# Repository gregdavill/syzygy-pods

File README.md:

# SYZYGY pods
This repository contains open source hardware SYZYGY pods designs
All repos are in KiCad format, some may require the use of KiCad nightly

---

SYZYGY is an FPGA expansion standard for medium to high speed interfaces. Learn more and check out the specifications here: [https://syzygyfpga.io/](https://syzygyfpga.io/)

* __lvds-10.1"-panel__ - 10.1" 1280x800 LVDS LCD + PMIC
* __ds90c124-deserializer__ - 1 to 24bit deserialzer
* __sii9022a__ - HDMI transmitter
* __can__ - MCP25625 based CAN controller

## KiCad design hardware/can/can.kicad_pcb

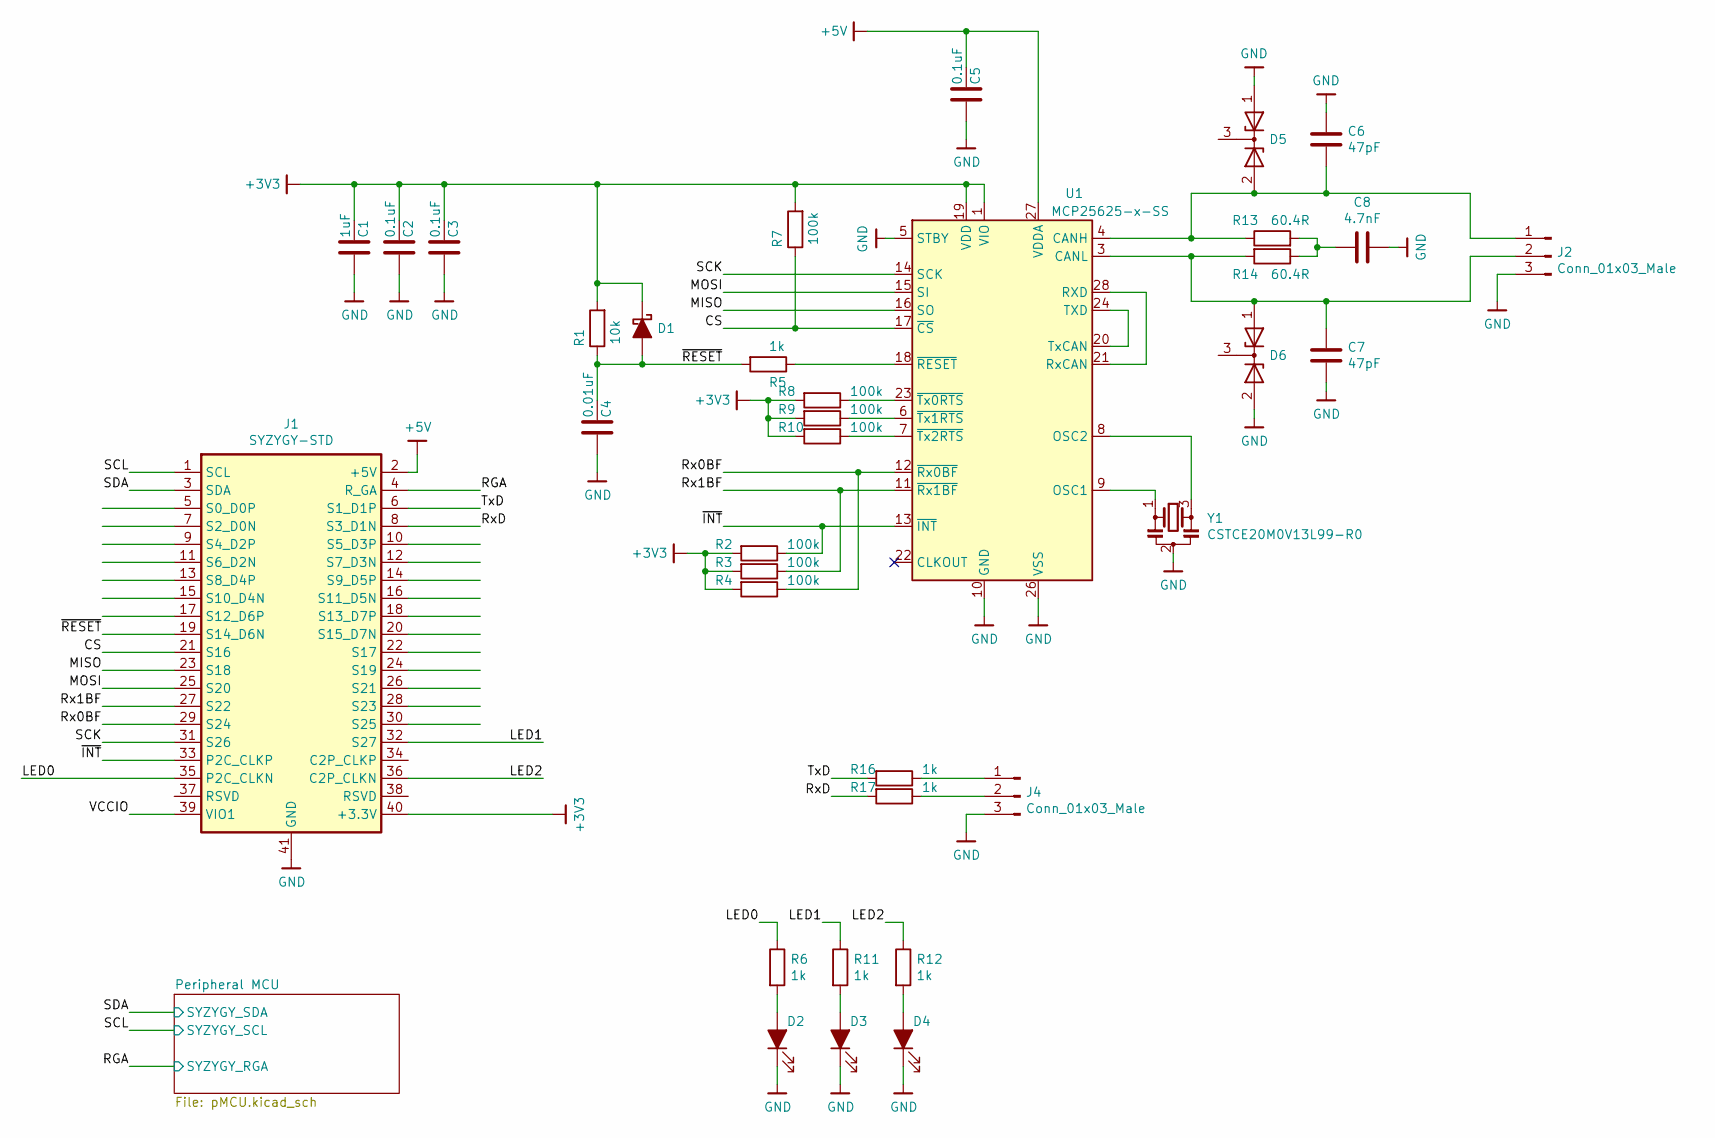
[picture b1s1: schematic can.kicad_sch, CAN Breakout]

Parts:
C1: 1uF; C_0402_1005Metric
C2, C3, C5: 0.1uF; C_0402_1005Metric
C4: 0.01uF; C_0402_1005Metric
C6, C7: 47pF; C_0805_2012Metric
C8: 4.7nF; C_0402_1005Metric
D1: D_Schottky_ALT; D_SOD-523
D2, D3, D4: LED_ALT; LED_0402_1005Metric
D5, D6: D_Zener_x2_KCom_AAK; SOT-23
J1: SYZYGY-STD; SYZYGY_standard_pod
J2: Conn_01x03_Male; PhoenixContact_MCV_1,5_3-G-3.5_1x03_P3.50mm_Vertical
J4: Conn_01x03_Male; PinHeader_1x03_P2.54mm_Vertical
R1: 10k; R_0402_1005Metric
R2, R3, R4, R7, R8, R9, R10: 100k; R_0402_1005Metric
R5, R6, R11, R12, R16, R17: 1k; R_0402_1005Metric
R13, R14: 60.4R; R_0805_2012Metric
U1: MCP25625-x-SS; SSOP-28_5.3x10.2mm_P0.65mm
Y1: CSTCE20M0V13L99-R0; Resonator_SMD_muRata_CSTxExxV-3Pin_3.0x1.1mm

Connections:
+3V3: C1.1, C2.1, C3.1, D1.1 (K), J1.40 (+3.3V), R1.2, R2.2, R3.2, R4.2, R7.2, R8.2, R9.2, R10.2, U1.1 (VIO), U1.19 (VDD); also elsewhere on the board
+5V: C5.1, J1.2 (+5V), U1.27 (VDDA)
/CS: J1.21 (S16), R7.1, U1.17 (~CS)
/LED0: J1.35 (P2C_CLKN), R6.1
/LED1: J1.32 (S27), R11.1
/LED2: J1.36 (C2P_CLKN), R12.1
/MISO: J1.23 (S18), U1.16 (SO)
/MOSI: J1.25 (S20), U1.15 (SI)
/RGA: J1.4 (R_GA); also elsewhere on the board
/Rx0BF: J1.29 (S24), R4.1, U1.12 (~Rx0BF)
/Rx1BF: J1.27 (S22), R3.1, U1.11 (~Rx1BF)
/RxD: J1.8 (S3_D1N), R17.2
/SCK: J1.31 (S26), U1.14 (SCK)
/SCL: J1.1 (SCL); also elsewhere on the board
/SDA: J1.3 (SDA); also elsewhere on the board
/TxD: J1.6 (S1_D1P), R16.2
/~INT: J1.33 (P2C_CLKP), R2.1, U1.13 (~INT)
/~RESET: C4.1, D1.2 (A), J1.19 (S14_D6N), R1.1, R5.2
GND: C1.2, C2.2, C3.2, C4.2, C5.2, C6.2, C7.1, C8.2, D2.1 (K), D3.1 (K), D4.1 (K), D5.1 (A), D6.2 (A), J1.41 (GND), J2.3, J4.3, U1.5 (STBY), U1.10 (GND), U1.26 (VSS), Y1.2; also elsewhere on the board
unnamed: C6.1, D5.2 (A), J2.1, R13.1, U1.4 (CANH)
unnamed: C7.2, D6.1 (A), J2.2, R14.2, U1.3 (CANL)
unnamed: C8.1, R13.2, R14.1
unnamed: D2.2 (A), R6.2
unnamed: D3.2 (A), R11.2
unnamed: D4.2 (A), R12.2
unnamed: J4.1, R16.1
unnamed: J4.2, R17.1
unnamed: R5.1, U1.18 (~RESET)
unnamed: R8.1, U1.23 (~Tx0RTS)
unnamed: R9.1, U1.6 (~Tx1RTS)
unnamed: R10.1, U1.7 (~Tx2RTS)
unnamed: U1.8 (OSC2), Y1.3
unnamed: U1.9 (OSC1), Y1.1
unnamed: U1.20 (TxCAN), U1.24 (TXD)
unnamed: U1.21 (RxCAN), U1.28 (RXD)

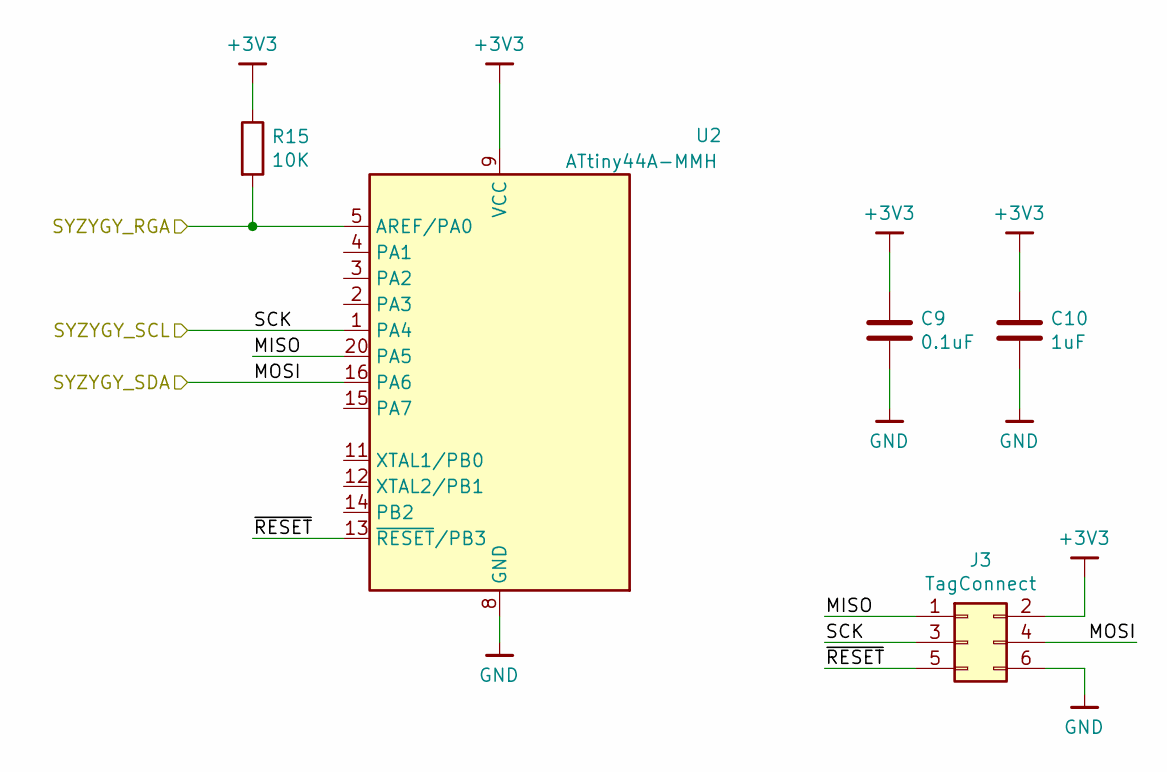
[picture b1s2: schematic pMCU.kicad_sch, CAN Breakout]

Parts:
C9: 0.1uF; C_0402_1005Metric
C10: 1uF; C_0402_1005Metric
J3: TagConnect; TC2030-NL_SMALL
R15: 10K; R_0402_1005Metric
U2: ATtiny44A-MMH; QFN-20-1EP_3x3mm_P0.45mm_EP1.6x1.6mm

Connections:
+3V3: C9.1, C10.1, J3.2, R15.1, U2.9 (VCC); also elsewhere on the board
/Peripheral MCU/MISO: J3.1, U2.20 (PA5)
/Peripheral MCU/~RESET: J3.5, U2.13 (~RESET~/PB3)
/RGA: R15.2, U2.5 (AREF/PA0); also elsewhere on the board
/SCL: J3.3, U2.1 (PA4); also elsewhere on the board
/SDA: J3.4, U2.16 (PA6); also elsewhere on the board
GND: C9.2, C10.2, J3.6, U2.8 (GND), U2.21 (GND); also elsewhere on the board

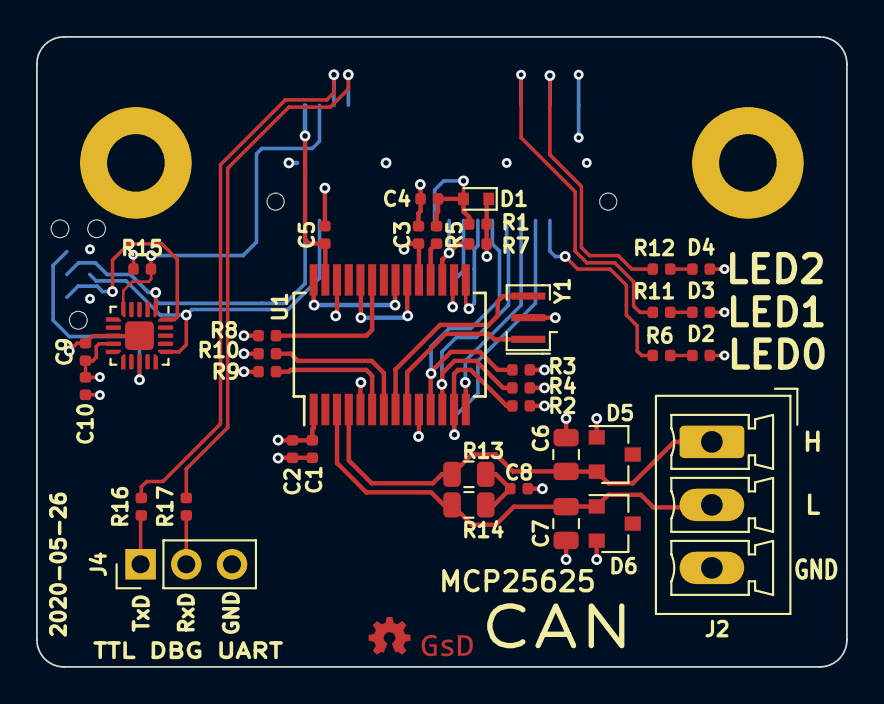
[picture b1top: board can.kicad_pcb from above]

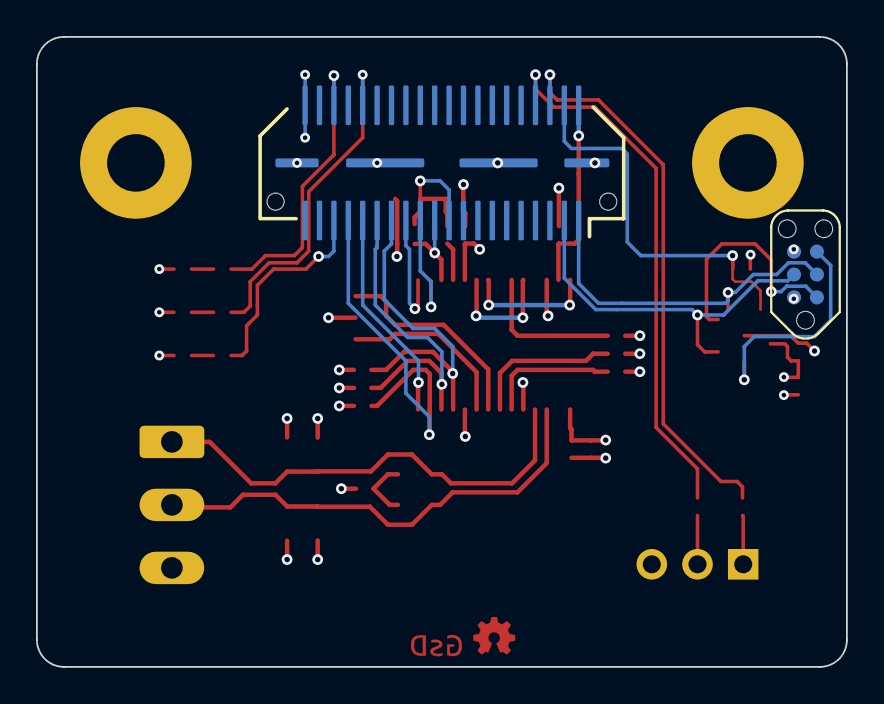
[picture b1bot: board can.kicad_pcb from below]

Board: 4 copper layers, 45.0 x 35.0 mm, 40 parts (2 on the bottom side), 37 nets.

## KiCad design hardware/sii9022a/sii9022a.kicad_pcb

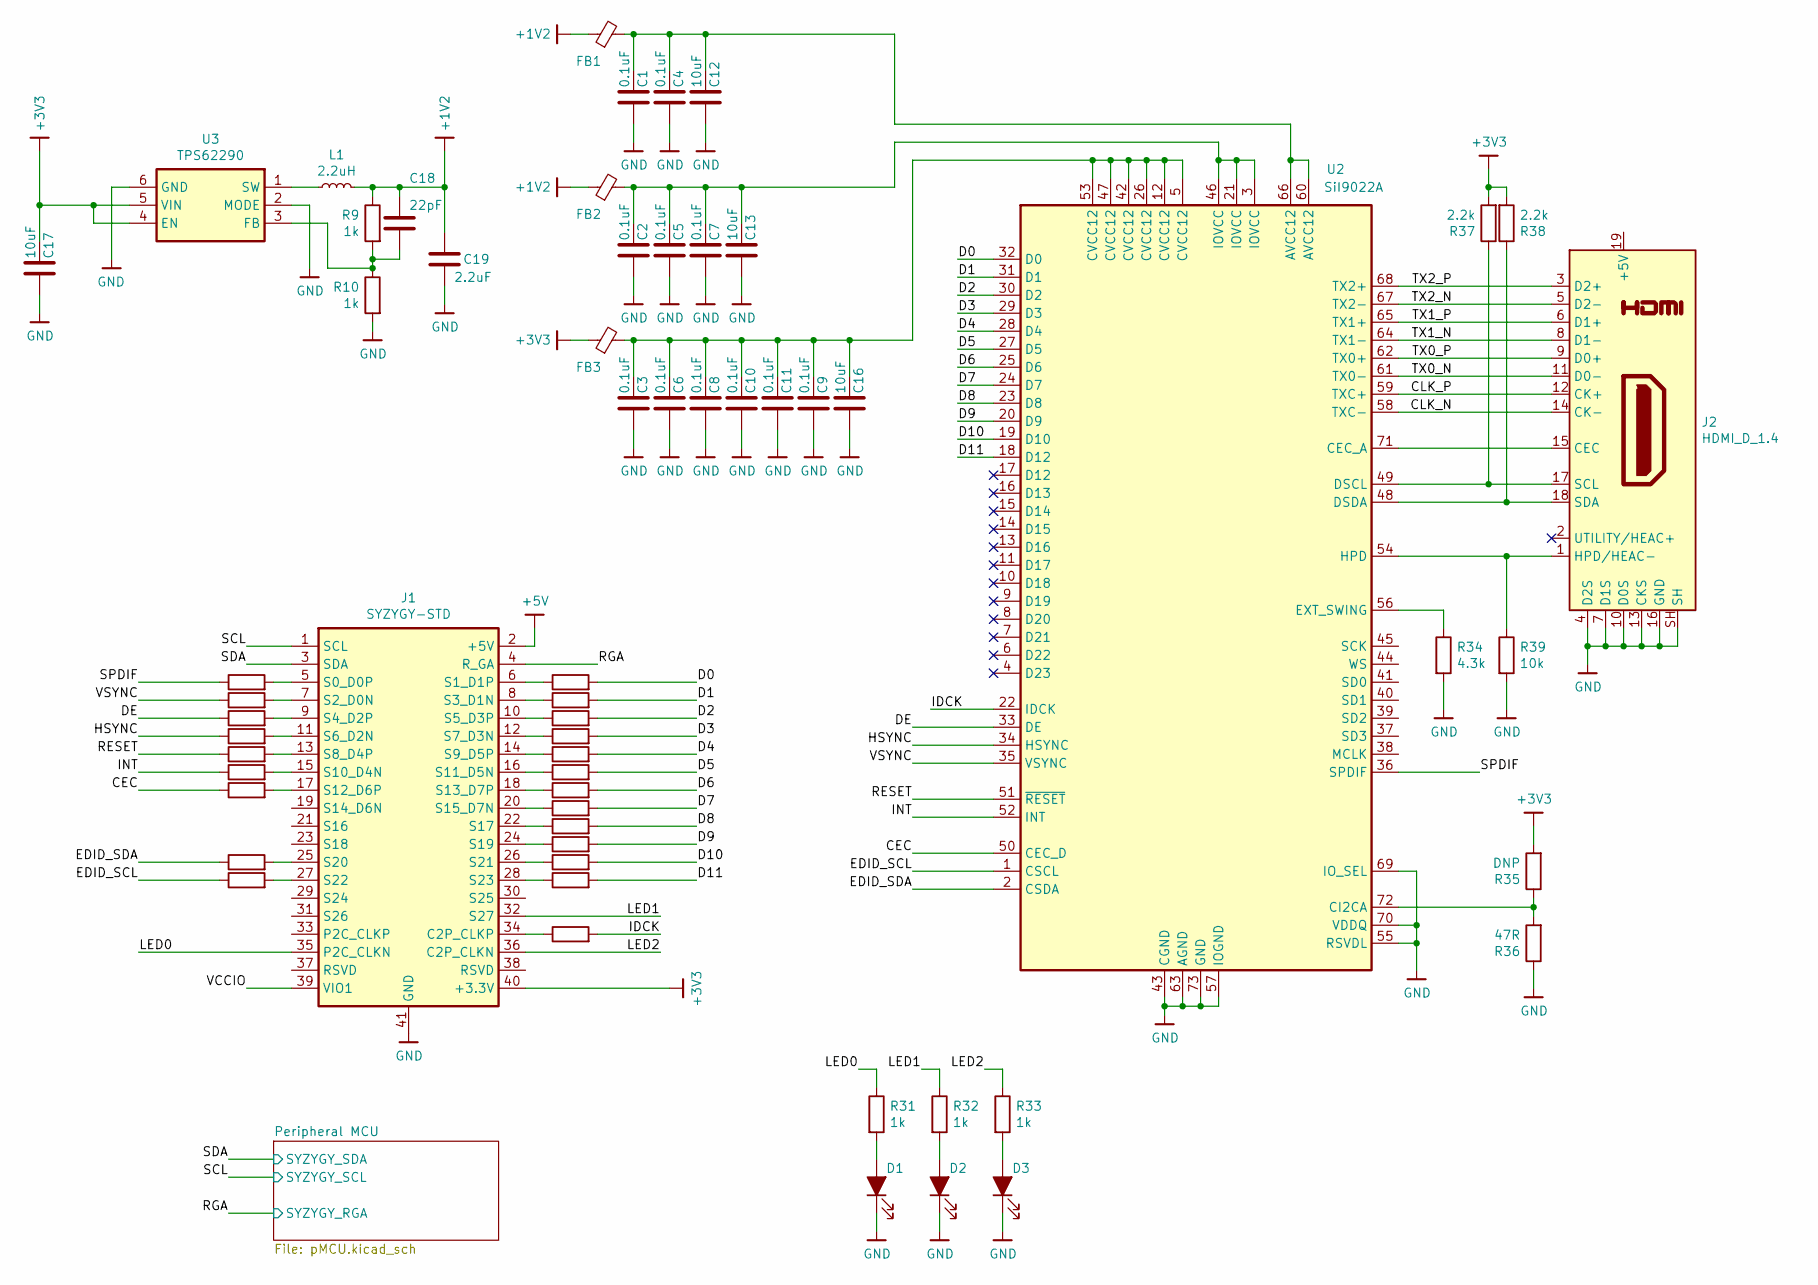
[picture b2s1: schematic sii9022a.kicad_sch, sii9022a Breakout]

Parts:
C1, C2, C3, C4, C5, C6, C7, C8, C9, C10, C11: 0.1uF; C_0402_1005Metric
C12, C13, C16, C17: 10uF; C_0603_1608Metric
C18: 22pF; C_0402_1005Metric
C19: 2.2uF; C_0402_1005Metric
D1, D2, D3: LED_ALT; LED_0402_1005Metric
FB1, FB2, FB3: 1k @ 100MHz; L_0402_1005Metric
J1: SYZYGY-STD; SYZYGY_standard_pod
J2: HDMI_D_1.4; HDMI_Micro-D_Molex_46765-1x01
L1: 2.2uH; L_0805_2012Metric
R2, R3, R4, R5, R6, R7, R8, R12, R13, R17, R18, R19, R20, R21, R22, R23, R24, R25, R26, R27, R28, R30, R36: 47R; R_0402_1005Metric
R9, R10, R31, R32, R33: 1k; R_0402_1005Metric
R34: 4.3k; R_0402_1005Metric
R35: DNP; R_0402_1005Metric
R37, R38: 2.2k; R_0402_1005Metric
R39: 10k; R_0402_1005Metric
U2: SiI9022A; QFN-72-1EP_10x10mm_P0.5mm_EP6x6mm
U3: TPS62290; WSON-6-1EP_2x2mm_P0.65mm_EP1x1.6mm_ThermalVias

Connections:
+1V2: C18.1, C19.1, FB1.1, FB2.1, L1.2, R9.1
+3V3: C17.1, FB3.1, J1.40 (+3.3V), R35.2, R37.2, R38.2, U3.4 (EN), U3.5 (VIN); also elsewhere on the board
/CEC: R8.1, U2.50 (CEC_D)
/CLK_N: J2.14 (CK-), U2.58 (TXC-)
/CLK_P: J2.12 (CK+), U2.59 (TXC+)
/D0: R17.2, U2.32 (D0)
/D1: R18.2, U2.31 (D1)
/D2: R19.2, U2.30 (D2)
/D3: R20.2, U2.29 (D3)
/D4: R21.2, U2.28 (D4)
/D5: R22.2, U2.27 (D5)
/D6: R23.2, U2.25 (D6)
/D7: R24.2, U2.24 (D7)
/D8: R25.2, U2.23 (D8)
/D9: R26.2, U2.20 (D9)
/D10: R27.2, U2.19 (D10)
/D11: R28.2, U2.18 (D12)
/DE: R4.1, U2.33 (DE)
/EDID_SCL: R13.1, U2.1 (CSCL)
/EDID_SDA: R12.1, U2.2 (CSDA)
/HSYNC: R5.1, U2.34 (HSYNC)
/IDCK: R30.2, U2.22 (IDCK)
/INT: R7.1, U2.52 (INT)
/LED0: J1.35 (P2C_CLKN), R31.1
/LED1: J1.32 (S27), R32.1
/LED2: J1.36 (C2P_CLKN), R33.1
/RESET: R6.1, U2.51 (~RESET)
/RGA: J1.4 (R_GA); also elsewhere on the board
/SCL: J1.1 (SCL); also elsewhere on the board
/SDA: J1.3 (SDA); also elsewhere on the board
/SPDIF: R2.1, U2.36 (SPDIF)
/TX0_N: J2.11 (D0-), U2.61 (TX0-)
/TX0_P: J2.9 (D0+), U2.62 (TX0+)
/TX1_N: J2.8 (D1-), U2.64 (TX1-)
/TX1_P: J2.6 (D1+), U2.65 (TX1+)
/TX2_N: J2.5 (D2-), U2.67 (TX2-)
/TX2_P: J2.3 (D2+), U2.68 (TX2+)
/VSYNC: R3.1, U2.35 (VSYNC)
GND: C1.2, C2.2, C3.2, C4.2, C5.2, C6.2, C7.2, C8.2, C9.2, C10.2, C11.2, C12.2, C13.2, C16.2, C17.2, C19.2, D1.1 (K), D2.1 (K), D3.1 (K), J1.41 (GND), J2.4 (D2S), J2.7 (D1S), J2.10 (D0S), J2.13 (CKS), J2.16 (GND), J2.SH, R10.2, R34.2, R36.1, R39.2, U2.43 (CGND), U2.55 (RSVDL), U2.57 (IOGND), U2.63 (AGND), U2.69 (IO_SEL), U2.70 (VDDQ), U2.73 (GND), U3.2 (MODE), U3.6 (GND), U3.7 (GND); also elsewhere on the board
unnamed: C1.1, C4.1, C12.1, FB1.2, U2.60 (AVCC12), U2.66 (AVCC12)
unnamed: C3.1, C6.1, C8.1, C9.1, C10.1, C11.1, C16.1, FB3.2, U2.5 (CVCC12), U2.12 (CVCC12), U2.26 (CVCC12), U2.42 (CVCC12), U2.47 (CVCC12), U2.53 (CVCC12)
unnamed: C2.1, C5.1, C7.1, C13.1, FB2.2, U2.3 (IOVCC), U2.21 (IOVCC), U2.46 (IOVCC)
unnamed: C18.2, R9.2, R10.1, U3.3 (FB)
unnamed: D1.2 (A), R31.2
unnamed: D2.2 (A), R32.2
unnamed: D3.2 (A), R33.2
unnamed: J1.5 (S0_D0P), R2.2
unnamed: J1.6 (S1_D1P), R17.1
unnamed: J1.7 (S2_D0N), R3.2
unnamed: J1.8 (S3_D1N), R18.1
unnamed: J1.9 (S4_D2P), R4.2
unnamed: J1.10 (S5_D3P), R19.1
unnamed: J1.11 (S6_D2N), R5.2
unnamed: J1.12 (S7_D3N), R20.1
unnamed: J1.13 (S8_D4P), R6.2
unnamed: J1.14 (S9_D5P), R21.1
unnamed: J1.15 (S10_D4N), R7.2
unnamed: J1.16 (S11_D5N), R22.1
unnamed: J1.17 (S12_D6P), R8.2
unnamed: J1.18 (S13_D7P), R23.1
unnamed: J1.20 (S15_D7N), R24.1
unnamed: J1.22 (S17), R25.1
unnamed: J1.24 (S19), R26.1
unnamed: J1.25 (S20), R12.2
unnamed: J1.26 (S21), R27.1
unnamed: J1.27 (S22), R13.2
unnamed: J1.28 (S23), R28.1
unnamed: J1.34 (C2P_CLKP), R30.1
unnamed: J2.1 (HPD/HEAC-), R39.1, U2.54 (HPD)
unnamed: J2.15 (CEC), U2.71 (CEC_A)
unnamed: J2.17 (SCL), R37.1, U2.49 (DSCL)
unnamed: J2.18 (SDA), R38.1, U2.48 (DSDA)
unnamed: L1.1, U3.1 (SW)
unnamed: R34.1, U2.56 (EXT_SWING)
unnamed: R35.1, R36.2, U2.72 (CI2CA)

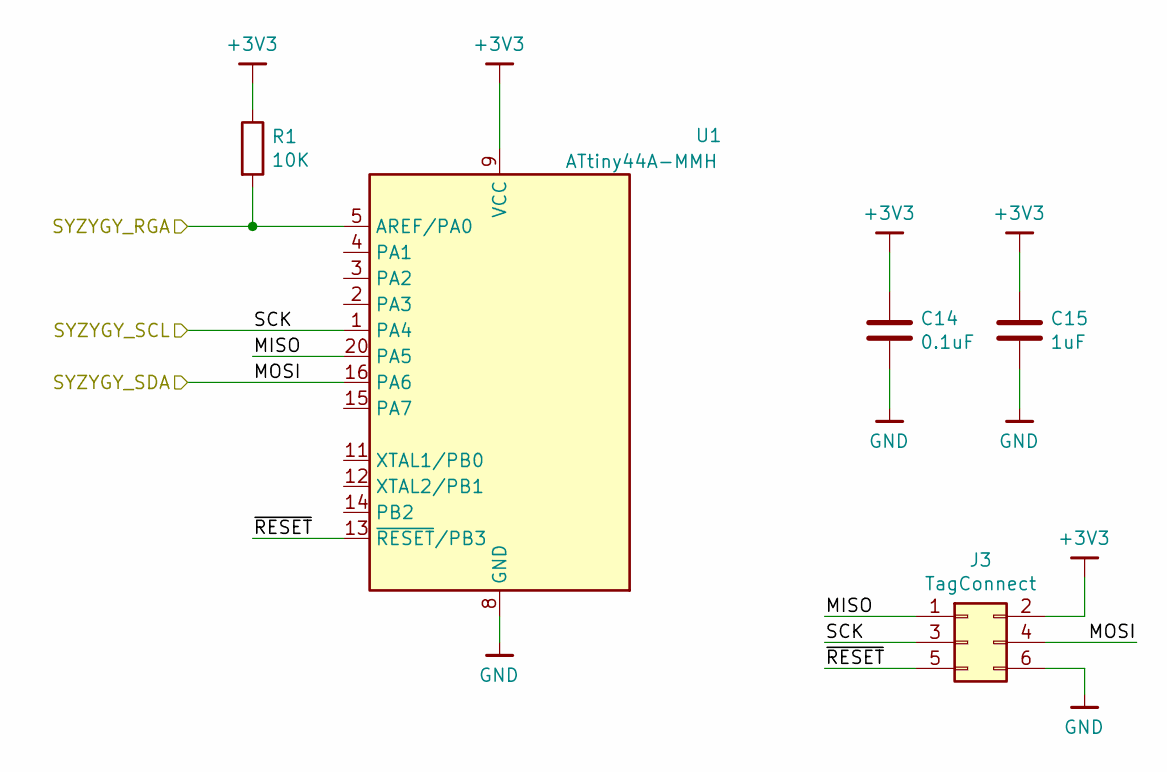
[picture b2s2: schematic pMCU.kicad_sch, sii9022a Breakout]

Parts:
C14: 0.1uF; C_0402_1005Metric
C15: 1uF; C_0402_1005Metric
J3: TagConnect; TC2030-NL_SMALL
R1: 10K; R_0402_1005Metric
U1: ATtiny44A-MMH; QFN-20-1EP_3x3mm_P0.45mm_EP1.6x1.6mm

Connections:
+3V3: C14.1, C15.1, J3.2, R1.1, U1.9 (VCC); also elsewhere on the board
/Peripheral MCU/MISO: J3.1, U1.20 (PA5)
/Peripheral MCU/~RESET: J3.5, U1.13 (~RESET~/PB3)
/RGA: R1.2, U1.5 (AREF/PA0); also elsewhere on the board
/SCL: J3.3, U1.1 (PA4); also elsewhere on the board
/SDA: J3.4, U1.16 (PA6); also elsewhere on the board
GND: C14.2, C15.2, J3.6, U1.8 (GND), U1.21 (GND); also elsewhere on the board

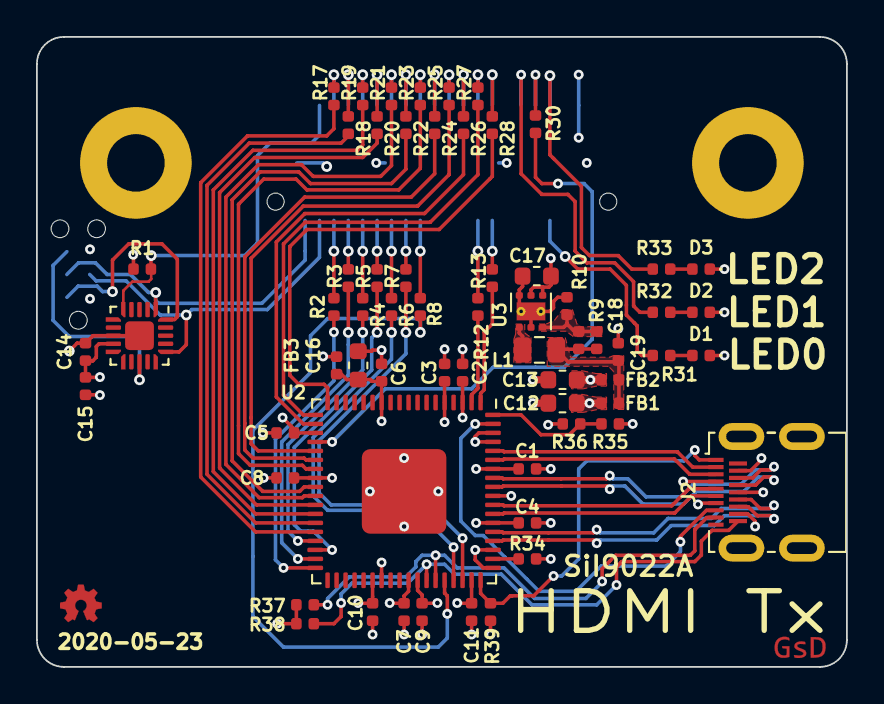
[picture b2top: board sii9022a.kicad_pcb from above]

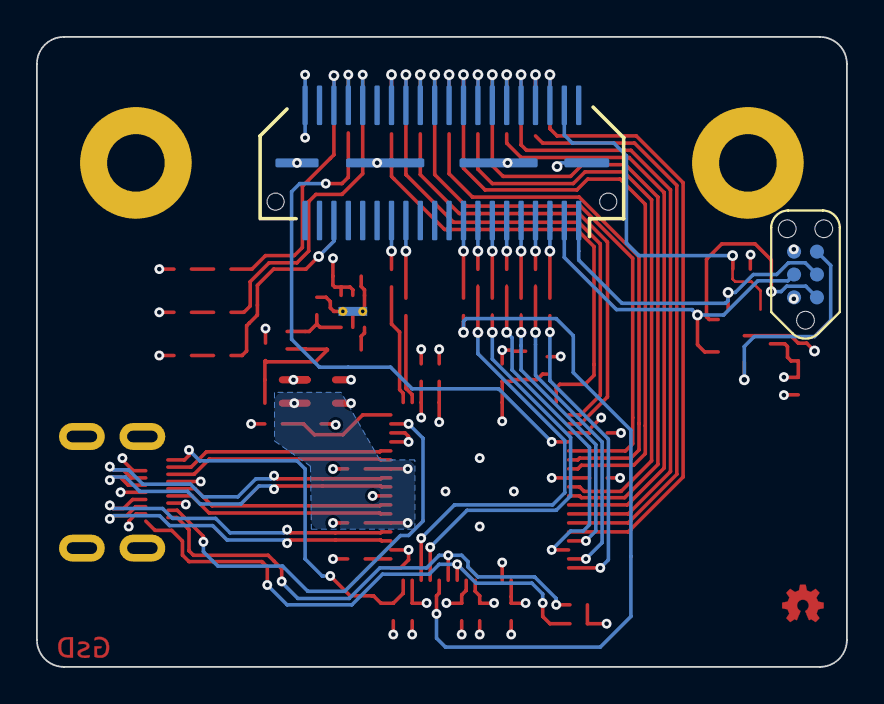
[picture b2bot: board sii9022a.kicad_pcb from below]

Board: 4 copper layers, 45.0 x 35.0 mm, 66 parts (2 on the bottom side), 77 nets.

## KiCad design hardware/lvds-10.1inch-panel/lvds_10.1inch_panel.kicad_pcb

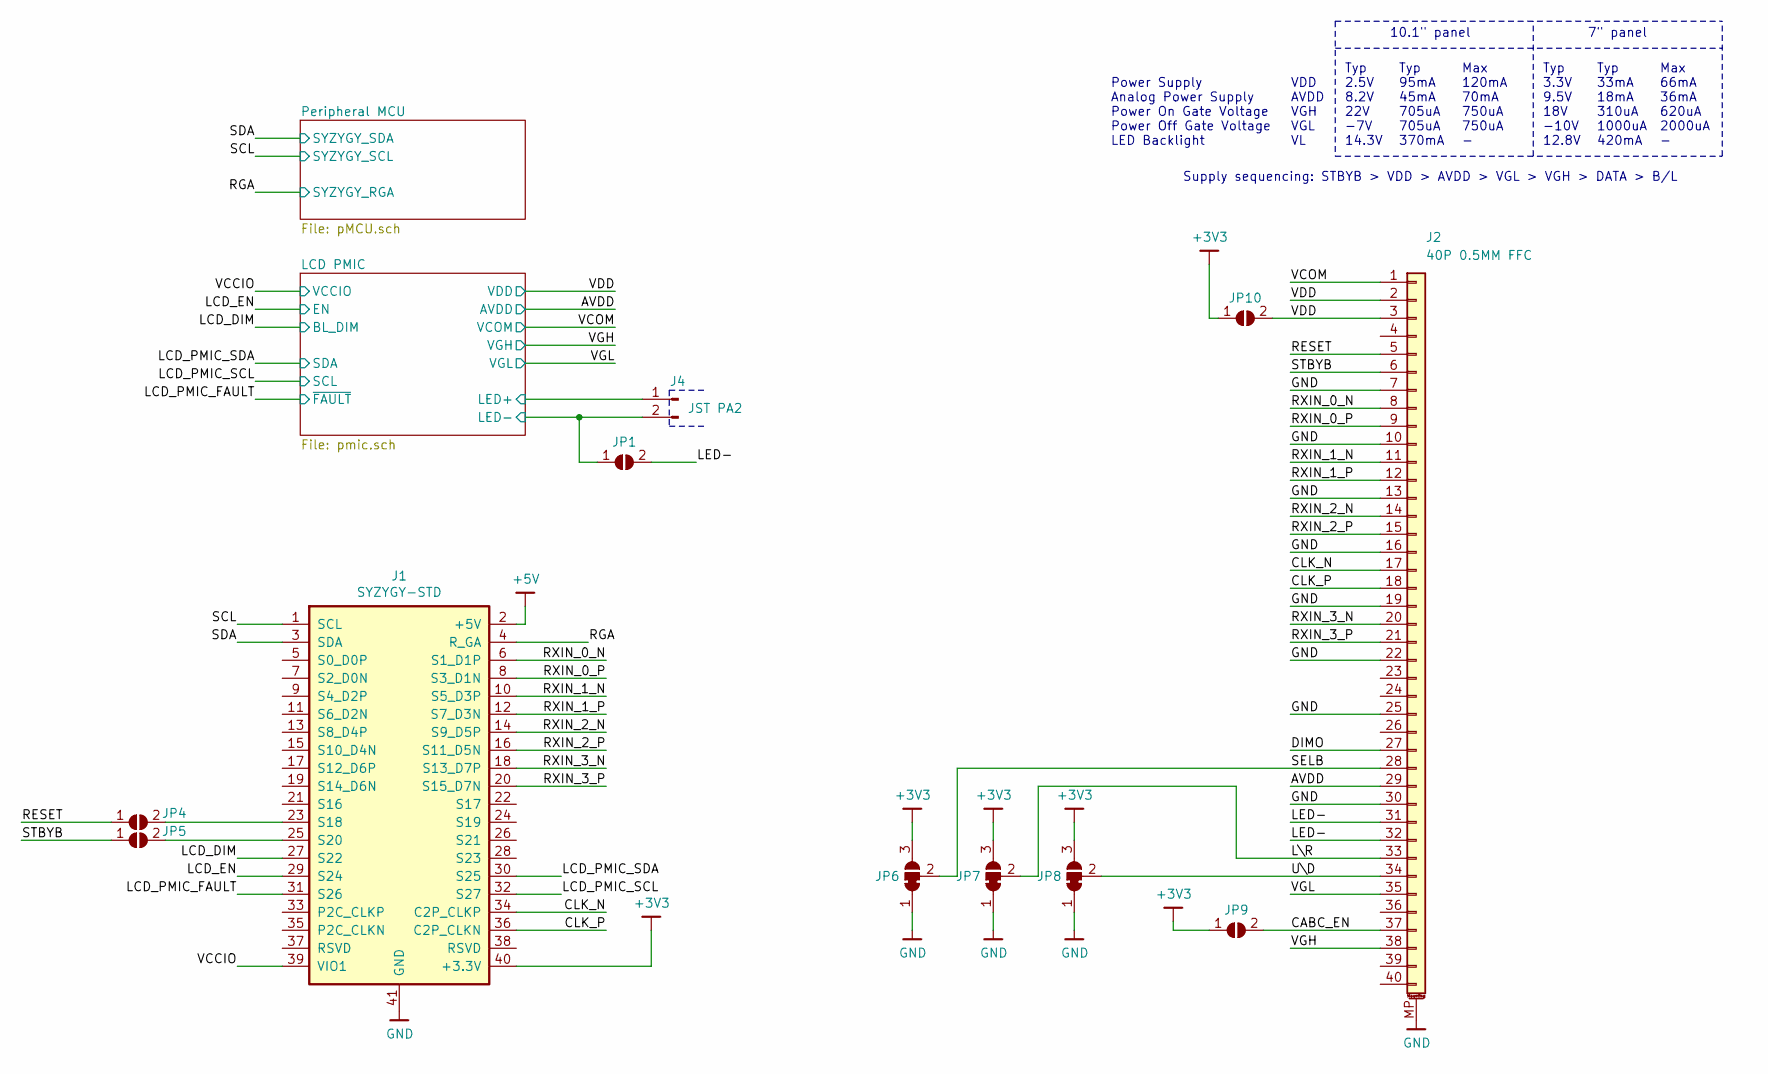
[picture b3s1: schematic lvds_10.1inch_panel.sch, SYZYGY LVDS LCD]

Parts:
J1: SYZYGY-STD; SYZYGY_standard_pod
J2: 40P 0.5MM FFC; FH28E-40S-0.5SH(05)
J4: JST PA2; SB02B-PASK-2
JP1, JP4, JP5, JP9: SolderJumper_2_Open; SolderJumper-2_P1.3mm_Open_RoundedPad1.0x1.5mm
JP6, JP7, JP8: SolderJumper_3_Bridged12; SolderJumper-3_P1.3mm_Bridged12_RoundedPad1.0x1.5mm
JP10: SolderJumper_2_Bridged; SolderJumper-2_P1.3mm_Open_RoundedPad1.0x1.5mm

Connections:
+3V3: J1.40 (+3.3V), JP6.3 (B), JP7.3 (B), JP8.3 (B), JP9.1 (A), JP10.1 (A); also elsewhere on the board
+5V: J1.2 (+5V); also elsewhere on the board
/AVDD: J2.29; also elsewhere on the board
/CABC_EN: J2.37, JP9.2 (B)
/CLK_N: J1.34 (C2P_CLKP), J2.17
/CLK_P: J1.36 (C2P_CLKN), J2.18
/DIMO: J2.27
/LCD PMIC/LED+: J4.1; also elsewhere on the board
/LCD PMIC/LED-: J4.2, JP1.1 (A); also elsewhere on the board
/LCD_DIM: J1.27 (S22); also elsewhere on the board
/LCD_EN: J1.29 (S24); also elsewhere on the board
/LCD_PMIC_FAULT: J1.31 (S26); also elsewhere on the board
/LCD_PMIC_SCL: J1.32 (S27); also elsewhere on the board
/LCD_PMIC_SDA: J1.30 (S25); also elsewhere on the board
/LED-: J2.31, J2.32, JP1.2 (B)
/L\R: J2.33, JP7.2 (C)
/RESET: J2.5, JP4.1 (A)
/RGA: J1.4 (R_GA); also elsewhere on the board
/RXIN_0_N: J1.6 (S1_D1P), J2.8
/RXIN_0_P: J1.8 (S3_D1N), J2.9
/RXIN_1_N: J1.10 (S5_D3P), J2.11
/RXIN_1_P: J1.12 (S7_D3N), J2.12
/RXIN_2_N: J1.14 (S9_D5P), J2.14
/RXIN_2_P: J1.16 (S11_D5N), J2.15
/RXIN_3_N: J1.18 (S13_D7P), J2.20
/RXIN_3_P: J1.20 (S15_D7N), J2.21
/SCL: J1.1 (SCL); also elsewhere on the board
/SDA: J1.3 (SDA); also elsewhere on the board
/SELB: J2.28, JP6.2 (C)
/STBYB: J2.6, JP5.1 (A)
/U\D: J2.34, JP8.2 (C)
/VCCIO: J1.39 (VIO1); also elsewhere on the board
/VCOM: J2.1; also elsewhere on the board
/VDD: J2.2, J2.3, JP10.2 (B); also elsewhere on the board
/VGH: J2.38; also elsewhere on the board
/VGL: J2.35; also elsewhere on the board
GND: J1.41 (GND), J2.7, J2.10, J2.13, J2.16, J2.19, J2.22, J2.25, J2.30, J2.MP (MountPin), JP6.1 (A), JP7.1 (A), JP8.1 (A); also elsewhere on the board
unnamed: J1.23 (S18), JP4.2 (B)
unnamed: J1.25 (S20), JP5.2 (B)

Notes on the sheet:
Power Supply Analog Power Supply Power On Gate Voltage Power Off Gate Voltage LED Backlight
VDD AVDD VGH VGL VL
Typ 2.5V 8.2V 22V -7V 14.3V
Typ 95mA 45mA 705uA 705uA 370mA
Max 120mA 70mA 750uA 750uA -
10.1" panel
Typ 3.3V 9.5V 18V -10V 12.8V
Typ 33mA 18mA 310uA 1000uA 420mA
Max 66mA 36mA 620uA 2000uA -
7" panel
Supply sequencing: STBYB > VDD > AVDD > VGL > VGH > DATA > B/L

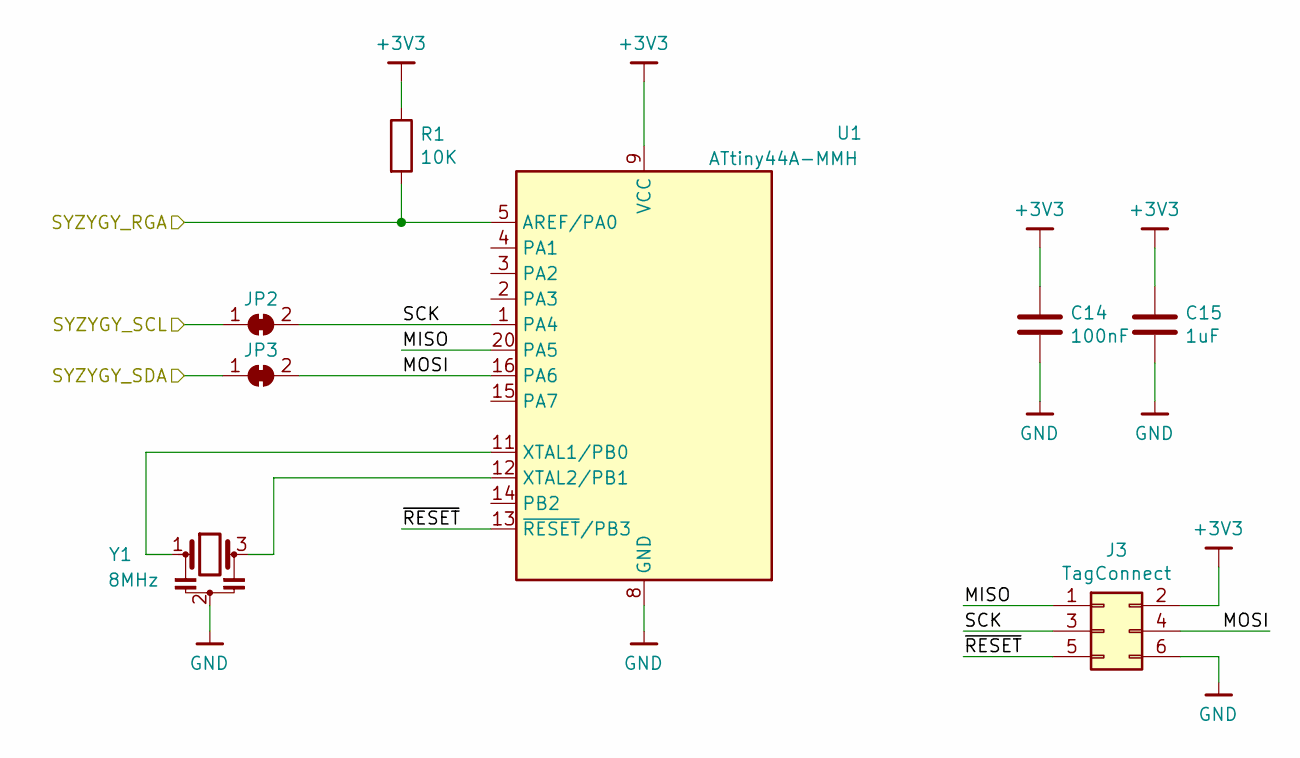
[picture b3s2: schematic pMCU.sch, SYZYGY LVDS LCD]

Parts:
C14: 100nF; C_0402
C15: 1uF; C_0402
J3: TagConnect; TC2030-NL_SMALL
JP2, JP3: SolderJumper_2_Bridged; SolderJumper-2_P1.3mm_Bridged_RoundedPad1.0x1.5mm
R1: 10K; R_0402
U1: ATtiny44A-MMH; QFN-20-1EP_3x3mm_P0.45mm_EP1.6x1.6mm
Y1: 8MHz; Resonator_SMD_muRata_CSTxExxV-3Pin_3.0x1.1mm

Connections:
+3V3: C14.1, C15.1, J3.2, R1.1, U1.9 (VCC); also elsewhere on the board
/Peripheral MCU/MISO: J3.1, U1.20 (PA5)
/Peripheral MCU/MOSI: J3.4, JP3.2 (B), U1.16 (PA6)
/Peripheral MCU/SCK: J3.3, JP2.2 (B), U1.1 (PA4)
/Peripheral MCU/~RESET: J3.5, U1.13 (~RESET~/PB3)
/RGA: R1.2, U1.5 (AREF/PA0); also elsewhere on the board
/SCL: JP2.1 (A); also elsewhere on the board
/SDA: JP3.1 (A); also elsewhere on the board
GND: C14.2, C15.2, J3.6, U1.8 (GND), U1.21 (GND), Y1.2; also elsewhere on the board
unnamed: U1.11 (XTAL1/PB0), Y1.1
unnamed: U1.12 (XTAL2/PB1), Y1.3

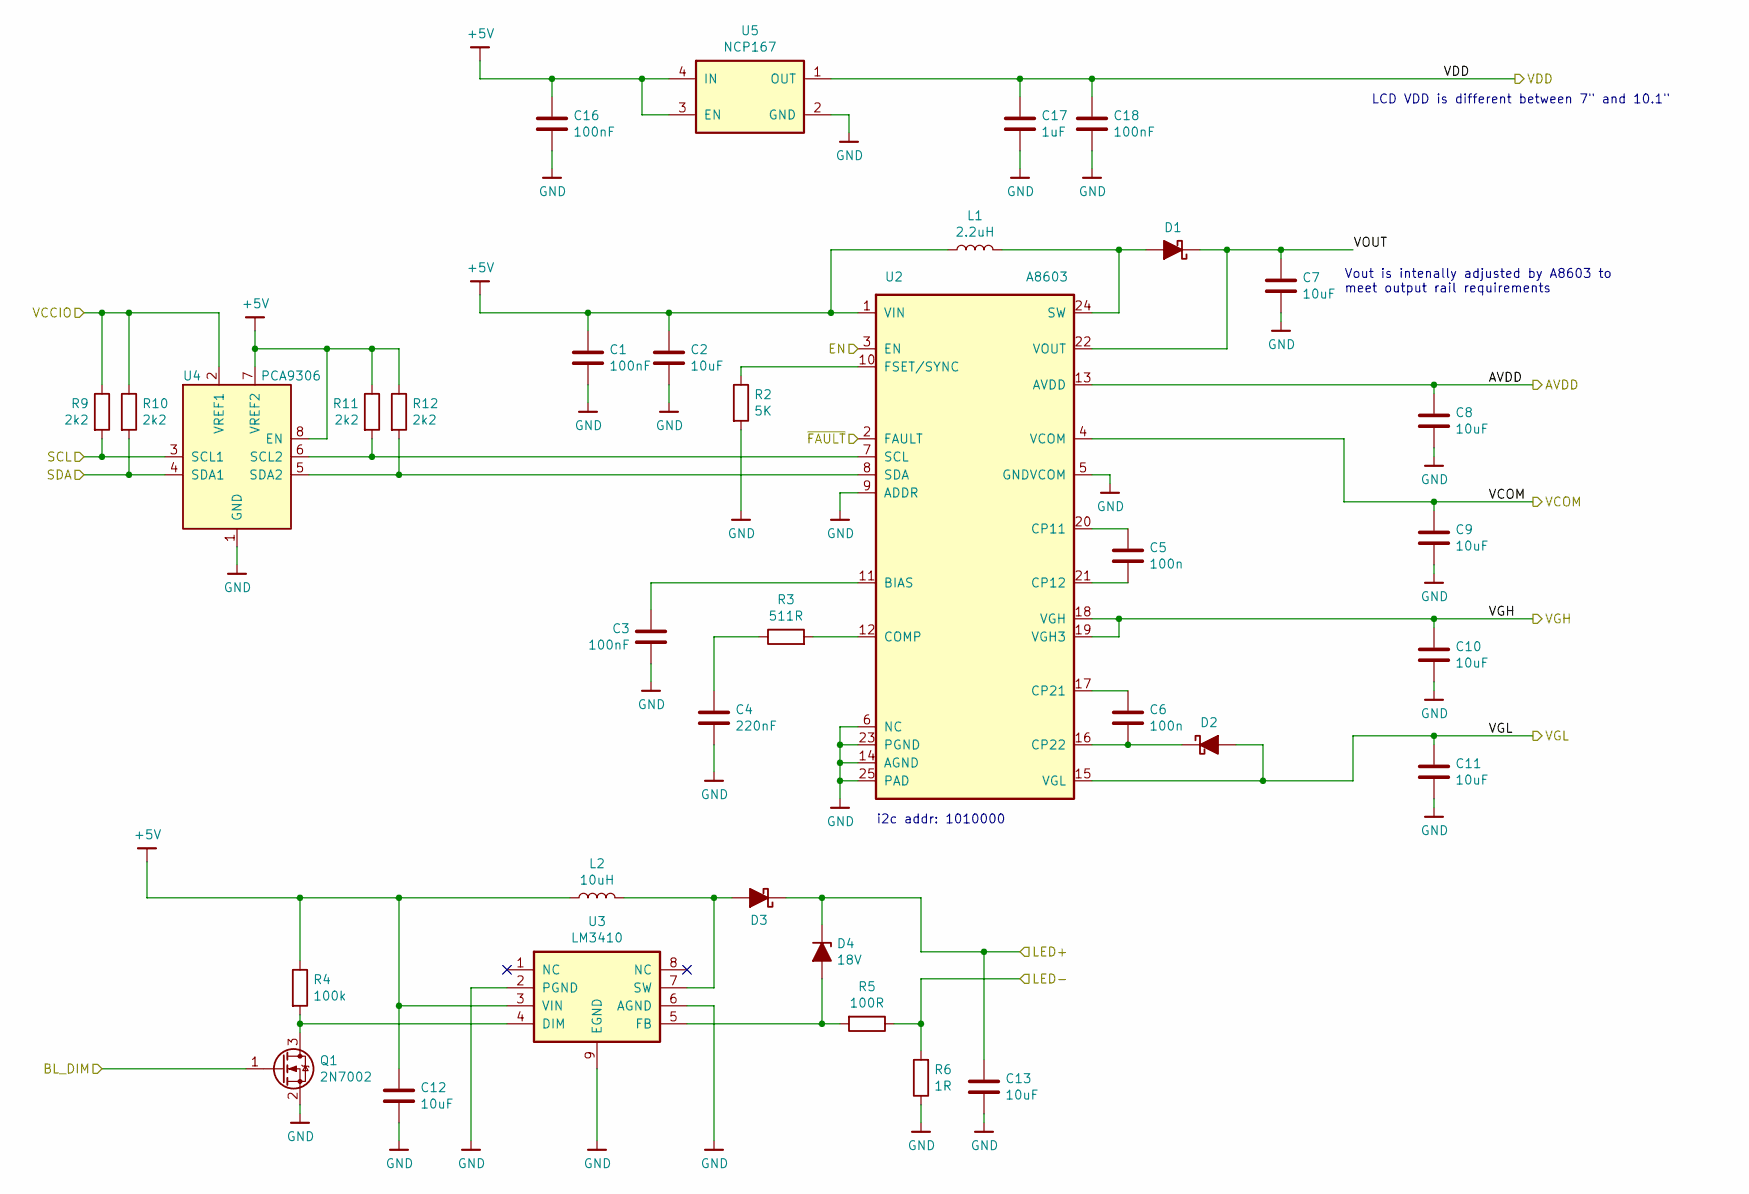
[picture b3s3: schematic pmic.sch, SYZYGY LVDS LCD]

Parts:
C1, C3, C16, C18: 100nF; C_0402
C2, C12: 10uF; C_0603
C4: 220nF; C_0402
C5, C6: 100n; C_0603
C7, C8, C9, C10, C11, C13: 10uF; C_0805
C17: 1uF; C_0402
D1, D2: D_Schottky_ALT; D_SOD-523
D3: D_Schottky_ALT; D_SOD-123
D4: 18V; D_SOD-123
L1: 2.2uH; L_Taiyo-Yuden_MD-3030
L2: 10uH; L_Taiyo-Yuden_MD-5050
Q1: 2N7002; SOT-23
R2: 5K; R_0402
R3: 511R; R_0402
R4: 100k; R_0402
R5: 100R; R_0402
R6: 1R; R_0402
R9, R10, R11, R12: 2k2; R_0402
U2: A8603; QFN-24-1EP_4x4mm_P0.5mm_EP2.6x2.6mm_ThermalVias
U3: LM3410; MSOP-8-1EP_3x3mm_P0.65mm_EP2.54x2.8mm_ThermalVias
U4: PCA9306; MSOP-8_3x3mm_P0.65mm
U5: NCP167; X2SON_4_1.0x1.0mm

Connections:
+5V: C1.1, C2.1, C12.1, C16.1, L1.1, L2.1, R4.1, R11.1, R12.1, U2.1 (VIN), U3.3 (VIN), U4.7 (VREF2), U4.8 (EN), U5.3 (EN), U5.4 (IN); also elsewhere on the board
/AVDD: C8.1, U2.13 (AVDD); also elsewhere on the board
/LCD PMIC/LED+: C13.1, D3.1 (K), D4.1 (K); also elsewhere on the board
/LCD PMIC/LED-: R5.1, R6.2; also elsewhere on the board
/LCD PMIC/VOUT: C7.1, D1.1 (K), U2.22 (VOUT)
/LCD_DIM: Q1.1 (G); also elsewhere on the board
/LCD_EN: U2.3 (EN); also elsewhere on the board
/LCD_PMIC_FAULT: U2.2 (FAULT); also elsewhere on the board
/LCD_PMIC_SCL: R9.2, U4.3 (SCL1); also elsewhere on the board
/LCD_PMIC_SDA: R10.2, U4.4 (SDA1); also elsewhere on the board
/VCCIO: R9.1, R10.1, U4.2 (VREF1); also elsewhere on the board
/VCOM: C9.1, U2.4 (VCOM); also elsewhere on the board
/VDD: C17.1, C18.1, U5.1 (OUT); also elsewhere on the board
/VGH: C10.1, U2.18 (VGH), U2.19 (VGH3); also elsewhere on the board
/VGL: C11.1, D2.2 (A), U2.15 (VGL); also elsewhere on the board
GND: C1.2, C2.2, C3.2, C4.2, C7.2, C8.2, C9.2, C10.2, C11.2, C12.2, C13.2, C16.2, C17.2, C18.2, Q1.2 (S), R2.2, R6.1, U2.5 (GNDVCOM), U2.6 (NC), U2.9 (ADDR), U2.14 (AGND), U2.23 (PGND), U2.25 (PAD), U3.2 (PGND), U3.6 (AGND), U3.9 (EGND), U4.1 (GND), U5.2 (GND); also elsewhere on the board
unnamed: C3.1, U2.11 (BIAS)
unnamed: C4.1, R3.1
unnamed: C5.1, U2.20 (CP11)
unnamed: C5.2, U2.21 (CP12)
unnamed: C6.1, U2.17 (CP21)
unnamed: C6.2, D2.1 (K), U2.16 (CP22)
unnamed: D1.2 (A), L1.2, U2.24 (SW)
unnamed: D3.2 (A), L2.2, U3.7 (SW)
unnamed: D4.2 (A), R5.2, U3.5 (FB)
unnamed: Q1.3 (D), R4.2, U3.4 (DIM)
unnamed: R2.1, U2.10 (FSET/SYNC)
unnamed: R3.2, U2.12 (COMP)
unnamed: R11.2, U2.7 (SCL), U4.6 (SCL2)
unnamed: R12.2, U2.8 (SDA), U4.5 (SDA2)

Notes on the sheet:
i2c addr: 1010000
Vout is intenally adjusted by A8603 to meet output rail requirements
LCD VDD is different between 7" and 10.1"
